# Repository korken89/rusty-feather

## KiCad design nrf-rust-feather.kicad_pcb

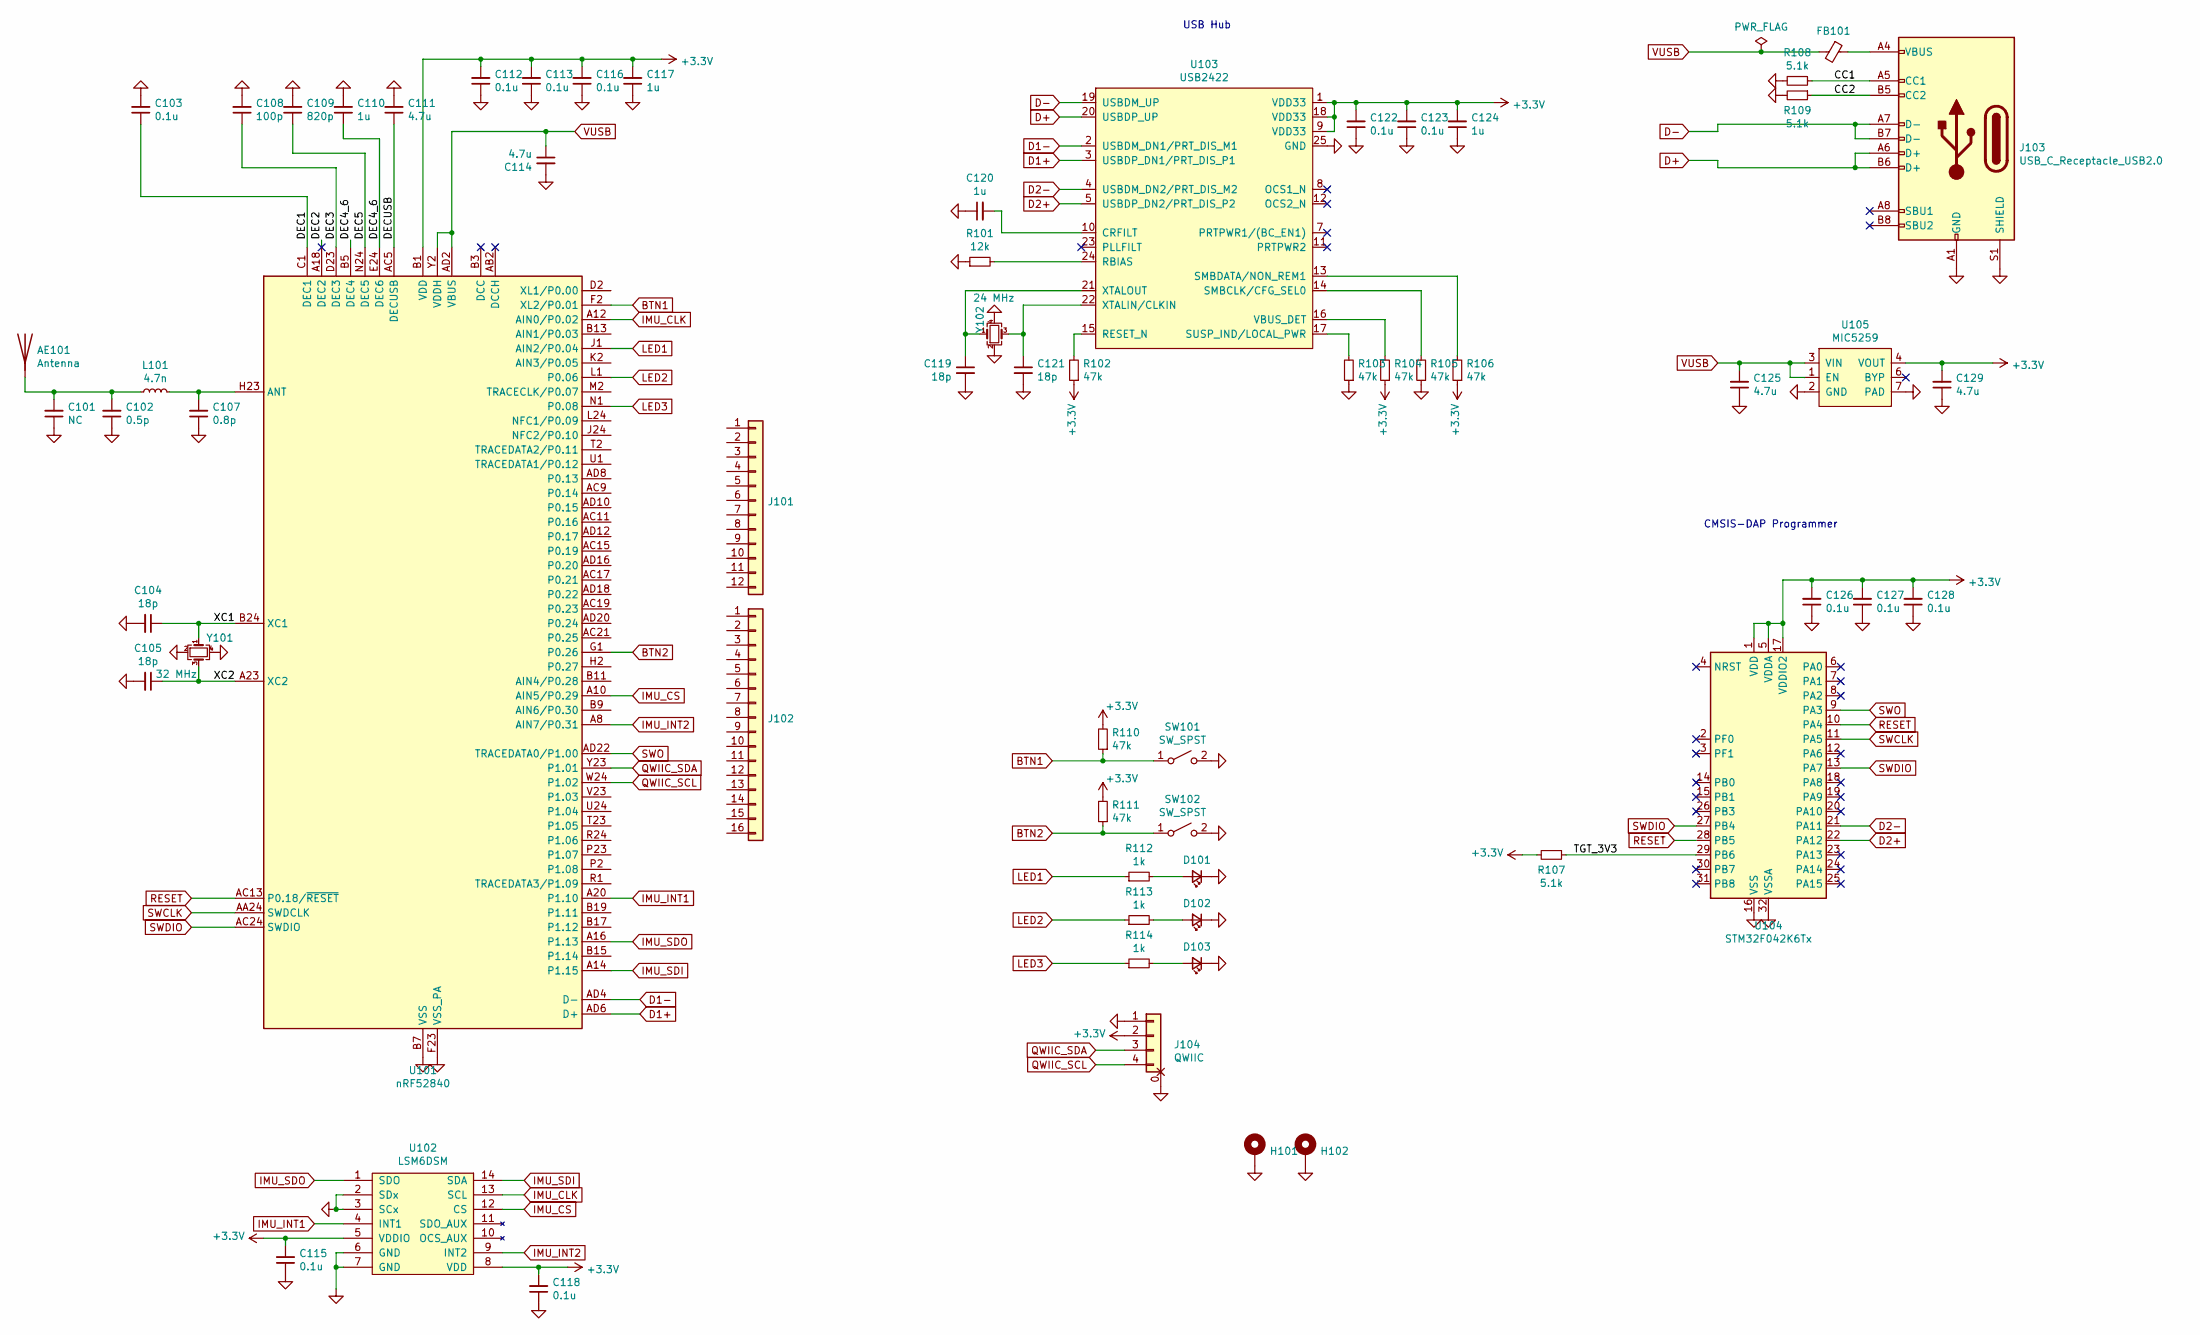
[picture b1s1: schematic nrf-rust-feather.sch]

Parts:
AE101: Antenna; R_1206; MPN AMCA31-2R450G-S1F-T3
C101: NC; C_0402
C102: 0.5p; C_0402
C103, C112, C113, C115, C116, C118, C122, C123, C126, C127, C128: 0.1u; C_0402
C104, C105, C119, C121: 18p; C_0402
C107: 0.8p; C_0402
C108: 100p; C_0402
C109: 820p; C_0402
C110, C117, C120, C124: 1u; C_0402
C111, C114, C125, C129: 4.7u; C_0603
D101, D102, D103: LED_Small; LED_0402_1005Metric
FB101: Ferrite_Bead_Small; R_0603
H101, H102: MountingHole_Pad; MountingHole_2.5mm_Pad
J101: Conn_01x12; 1x12_2.54mm
J102: Conn_01x16; 1x16_2.54mm
J103: USB_C_Receptacle_USB2.0; USB_C_Receptacle_USB4105; MPN C167321 (www.lcsc.com)
J104: QWIIC; SM04B-SRSS-TB
L101: 4.7n; R_0402
R101: 12k; R_0402
R102, R103, R104, R105, R106, R110, R111: 47k; R_0402
R107, R108, R109: 5.1k; R_0402
R112, R113, R114: 1k; R_0402
SW101, SW102: SW_SPST; SW_SPST_KMR2
U101: nRF52840; Nordic_AQFN-73-1EP_7x7mm_P0.5mm
U102: LSM6DSM; LGA-14-2.5x3
U103: USB2422; QFN-24-1EP_4x4mm_P0.5mm_EP2.6x2.6mm
U104: STM32F042K6Tx; LQFP-32_7x7mm_P0.8mm
U105: MIC5259; DFN-6-1EP_2x2mm_P0.65mm_EP1x1.6mm; MPN MIC5259-3.3YML-TR
Y101: 32 MHz; Crystal_4Pin_2.0x1.6mm
Y102: 24 MHz; Crystal_4Pin_2.0x1.6mm

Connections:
+3V3: C112.2, C113.2, C115.2, C116.2, C117.2, C118.2, C122.2, C123.2, C124.2, C126.2, C127.2, C128.2, C129.2, J104.2, R102.1, R104.1, R106.1, R107.2, R110.2, R111.2, U101.A22 (VDD), U101.AD14 (VDD), U101.AD23 (VDD), U101.B1 (VDD), U101.W1 (VDD), U102.5 (VDDIO), U102.8 (VDD), U103.1 (VDD33), U103.9 (VDD33), U103.18 (VDD33), U104.1 (VDD), U104.5 (VDDA), U104.17 (VDDIO2), U105.4 (VOUT)
/CC1: J103.A5 (CC1), R108.1
/CC2: J103.B5 (CC2), R109.1
/DEC1: C103.1, U101.C1 (DEC1)
/DEC2: U101.A18 (DEC2)
/DEC3: C108.1, U101.D23 (DEC3)
/DEC4_6: C110.1, U101.B5 (DEC4), U101.E24 (DEC6)
/DEC5: C109.1, U101.N24 (DEC5)
/DECUSB: C111.1, U101.AC5 (DECUSB)
/TGT_3V3: R107.1, U104.29 (PB6)
/XC1: C104.1, U101.B24 (XC1), Y101.1
/XC2: C105.1, U101.A23 (XC2), Y101.3
BTN1: R110.1, SW101.1 (A), U101.F2 (XL2/P0.01)
BTN2: R111.1, SW102.1 (A), U101.G1 (P0.26)
D1+: U101.AD6 (D+), U103.3 (USBDP_DN1/PRT_DIS_P1)
D1-: U101.AD4 (D-), U103.2 (USBDM_DN1/PRT_DIS_M1)
D2+: U103.5 (USBDP_DN2/PRT_DIS_P2), U104.22 (PA12)
D2-: U103.4 (USBDM_DN2/PRT_DIS_M2), U104.21 (PA11)
D+: J103.A6 (D+), J103.B6 (D+), U103.20 (USBDP_UP)
D-: J103.A7 (D-), J103.B7 (D-), U103.19 (USBDM_UP)
GND: C101.1, C102.1, C103.2, C104.2, C105.2, C107.1, C108.2, C109.2, C110.2, C111.2, C112.1, C113.1, C114.2, C115.1, C116.1, C117.1, C118.1, C119.2, C120.1, C121.2, C122.1, C123.1, C124.1, C125.1, C126.1, C127.1, C128.1, C129.1, D101.1 (K), D102.1 (K), D103.1 (K), H101.1, H102.1, J103.A1 (GND), J103.A12 (GND), J103.B1 (GND), J103.B12 (GND), J103.S1 (SHIELD), J104.0 (Mechanical), J104.1, R101.1, R103.1, R105.1, R108.2, R109.2, SW101.2 (B), SW102.2 (B), U101.B7 (VSS), U101.EP (VSS), U101.F23 (VSS_PA), U102.2 (SDx), U102.3 (SCx), U102.6 (GND), U102.7 (GND), U103.25 (GND), U104.16 (VSS), U104.32 (VSSA), U105.2 (GND), U105.7 (PAD), Y101.2, Y101.4, Y102.2, Y102.4
IMU_CLK: U101.A12 (AIN0/P0.02), U102.13 (SCL)
IMU_CS: U101.A10 (AIN5/P0.29), U102.12 (CS)
IMU_INT1: U101.A20 (P1.10), U102.4 (INT1)
IMU_INT2: U101.A8 (AIN7/P0.31), U102.9 (INT2)
IMU_SDI: U101.A14 (P1.15), U102.14 (SDA)
IMU_SDO: U101.A16 (P1.13), U102.1 (SDO)
LED1: R112.1, U101.J1 (AIN2/P0.04)
LED2: R113.1, U101.L1 (P0.06)
LED3: R114.1, U101.N1 (P0.08)
unnamed: AE101.1, C101.2, C102.2, L101.1
unnamed: C107.2, L101.2, U101.H23 (ANT)
unnamed: C119.1, U103.21 (XTALOUT), Y102.1
unnamed: C120.2, U103.10 (CRFILT)
unnamed: C121.1, U103.22 (XTALIN/CLKIN), Y102.3
unnamed: D101.2 (A), R112.2
unnamed: D102.2 (A), R113.2
unnamed: D103.2 (A), R114.2
unnamed: FB101.1, J103.A4 (VBUS), J103.A9 (VBUS), J103.B4 (VBUS), J103.B9 (VBUS)
unnamed: R101.2, U103.24 (RBIAS)
unnamed: R102.2, U103.15 (RESET_N)
unnamed: R103.2, U103.17 (SUSP_IND/LOCAL_PWR)
unnamed: R104.2, U103.16 (VBUS_DET)
unnamed: R105.2, U103.14 (SMBCLK/CFG_SEL0)
unnamed: R106.2, U103.13 (SMBDATA/NON_REM1)
QWIIC_SCL: J104.4, U101.W24 (P1.02)
QWIIC_SDA: J104.3, U101.Y23 (P1.01)
RESET: U101.AC13 (P0.18/~RESET), U104.10 (PA4), U104.28 (PB5)
SWCLK: U101.AA24 (SWDCLK), U104.11 (PA5)
SWDIO: U101.AC24 (SWDIO), U104.13 (PA7), U104.27 (PB4)
SWO: U101.AD22 (TRACEDATA0/P1.00), U104.9 (PA3)
VUSB: C114.1, C125.2, FB101.2, U101.AD2 (VBUS), U101.Y2 (VDDH), U105.1 (EN), U105.3 (VIN)

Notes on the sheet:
CMSIS-DAP Programmer
USB Hub

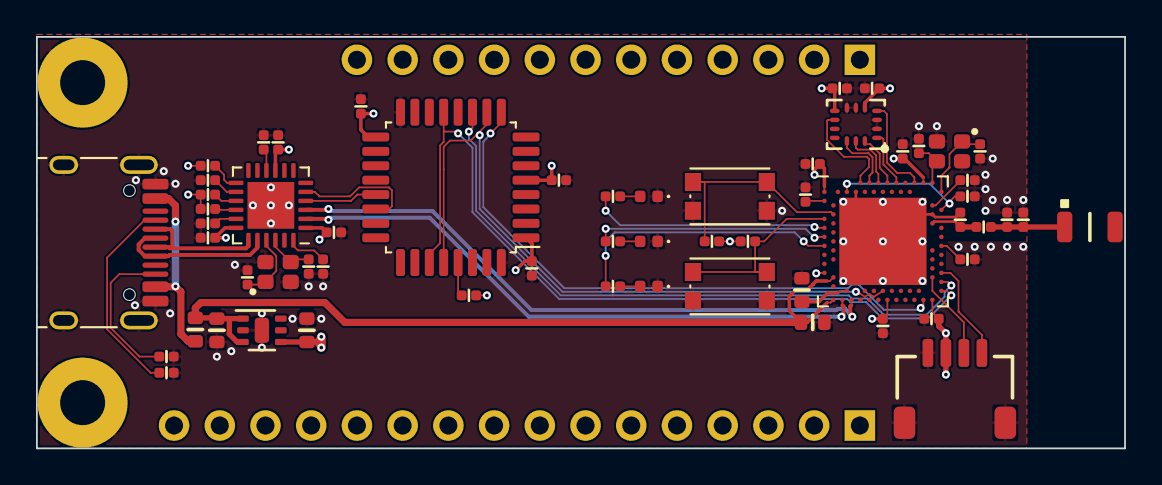
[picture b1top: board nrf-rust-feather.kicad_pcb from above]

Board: 4 copper layers, 60.5 x 22.9 mm, 63 parts (0 on the bottom side), 51 nets.

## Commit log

2020-07-08 Basic schematic done, pin headers needs signals
2020-07-08 Some layout, more parts
2020-07-22 Basic layout
